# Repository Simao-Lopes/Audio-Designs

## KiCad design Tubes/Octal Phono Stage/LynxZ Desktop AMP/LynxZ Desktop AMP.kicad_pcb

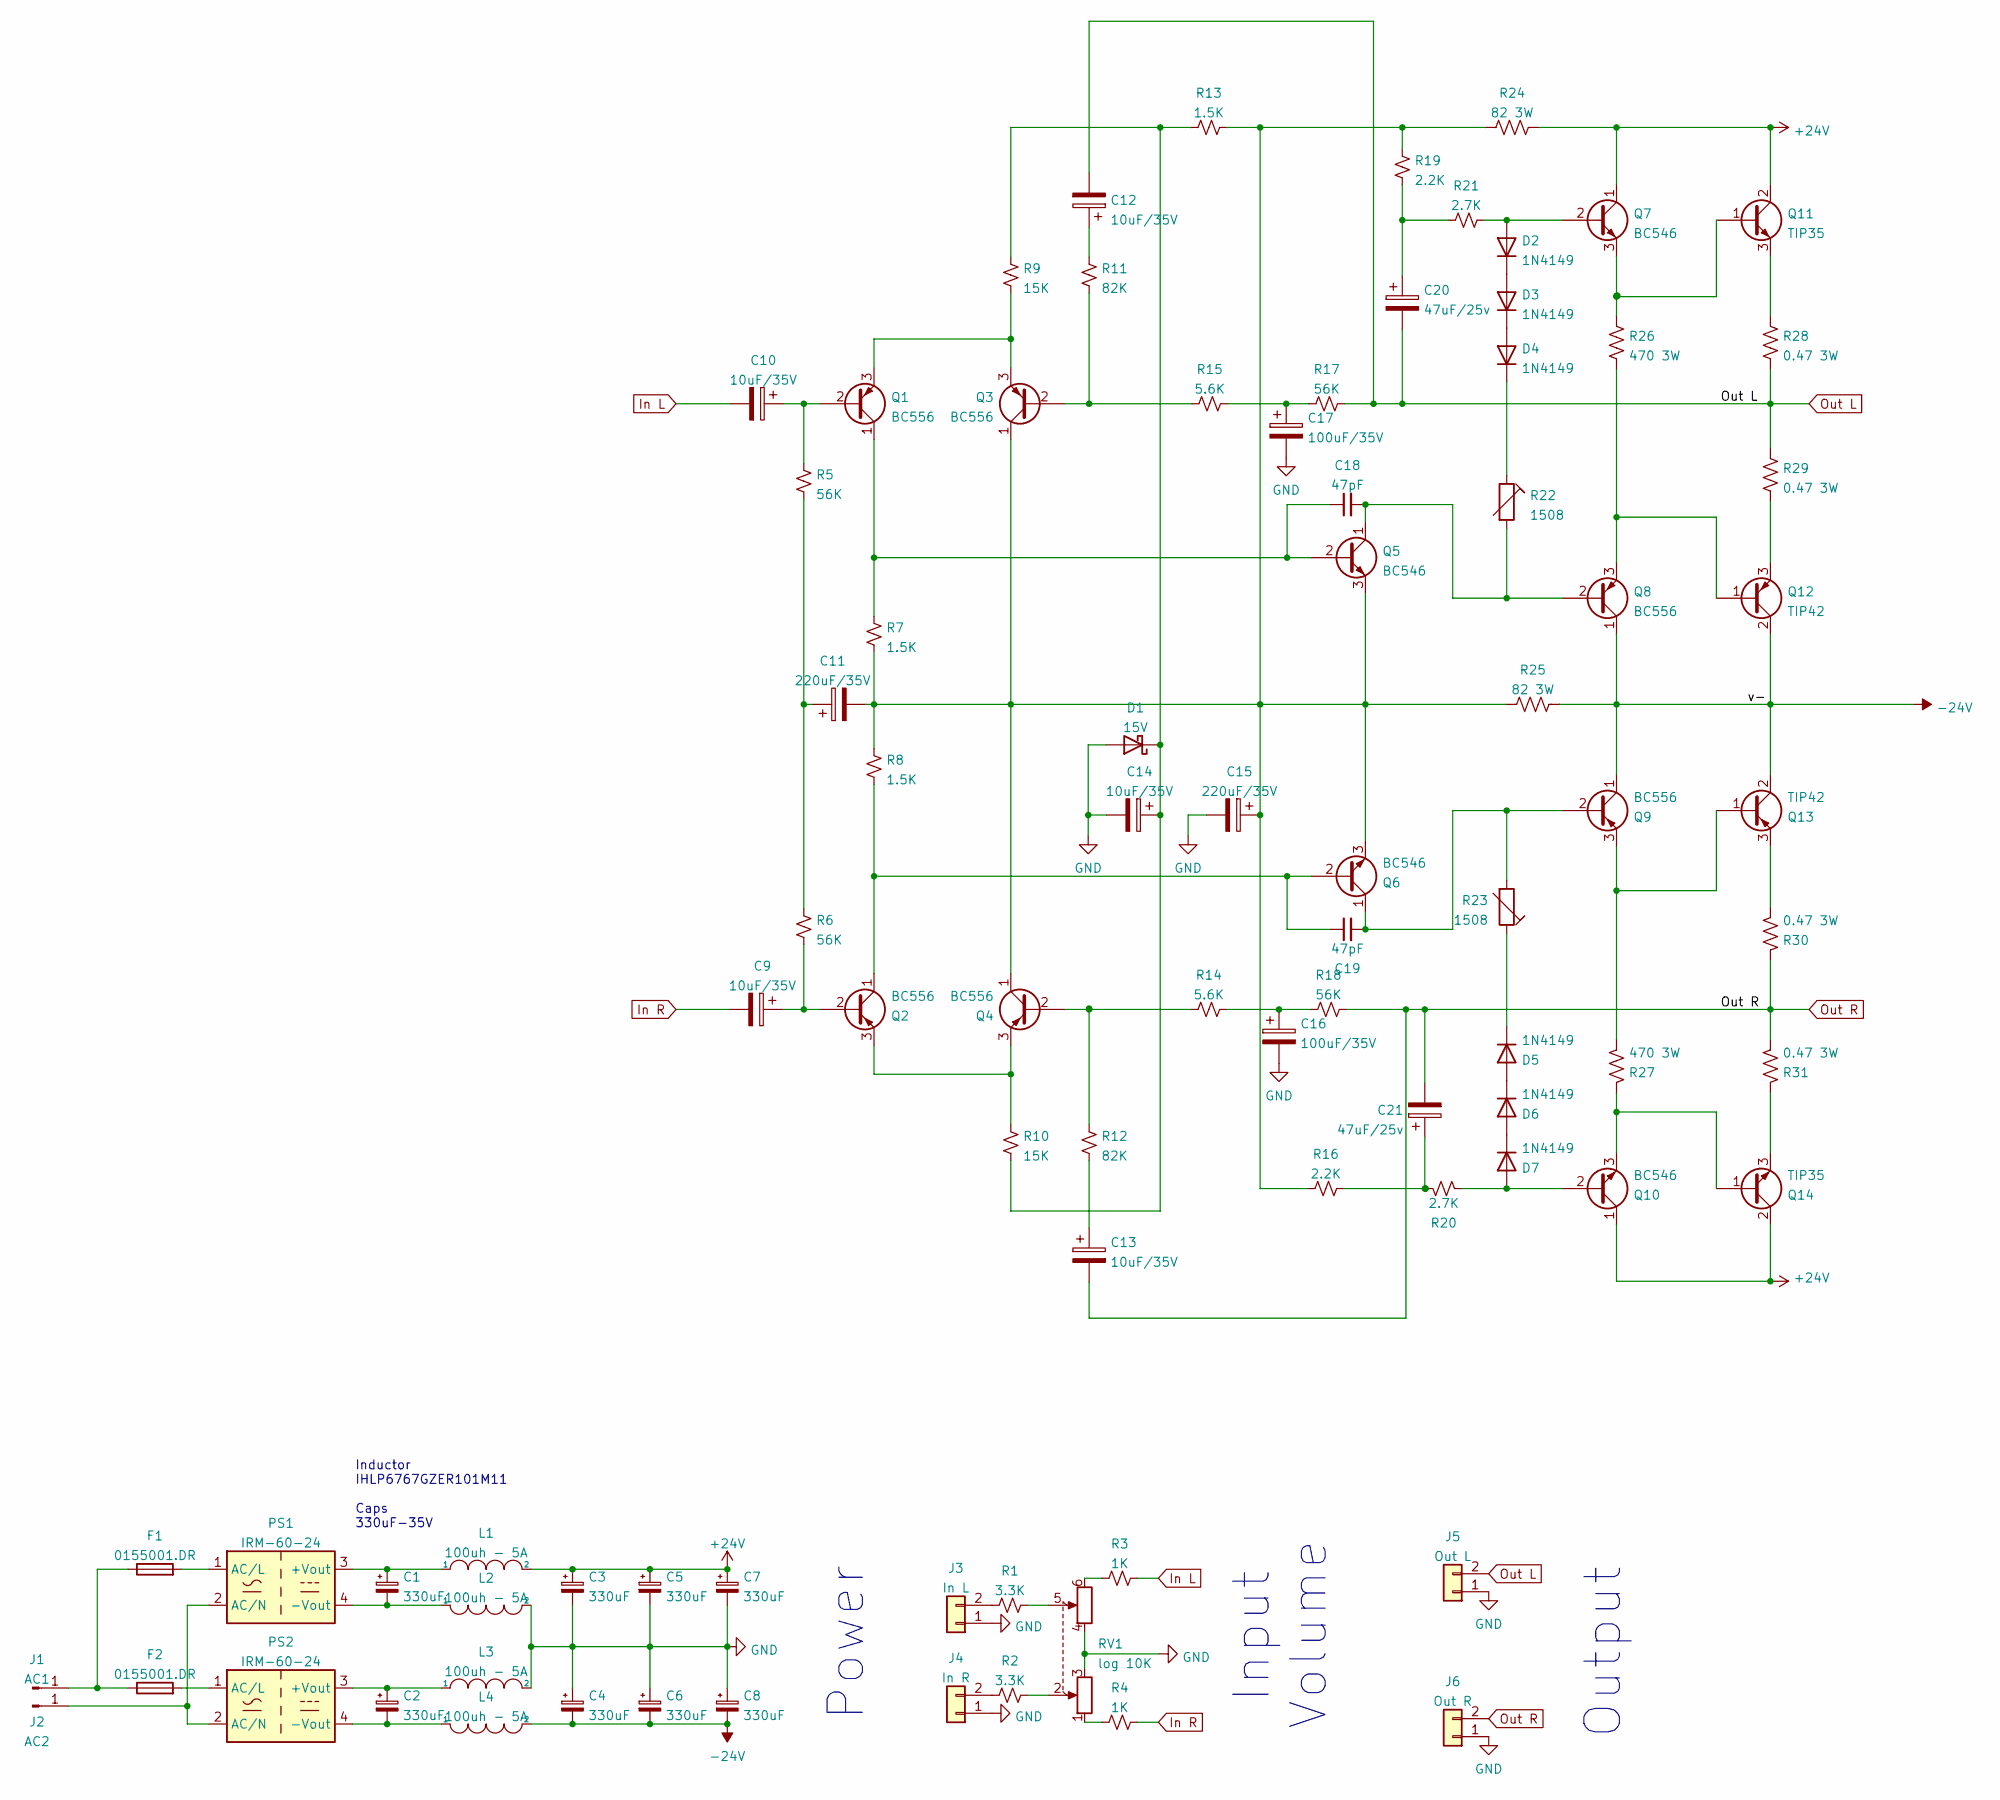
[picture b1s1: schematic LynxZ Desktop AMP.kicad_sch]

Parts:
C1, C2, C3, C4, C5, C6, C7, C8: 330uF; CP_Elec_16x17.5
C9, C10, C12, C13, C14: 10uF/35V; CP_Elec_5x5.3
C11, C15: 220uF/35V; CP_Elec_8x10
C16, C17: 100uF/35V; CP_Elec_8x10
C18, C19: 47pF; C_Rect_L7.2mm_W4.5mm_P5.00mm_FKS2_FKP2_MKS2_MKP2
C20, C21: 47uF/25v; CP_Elec_16x17.5
D1: 15V; D_SMA-SMB_Universal_Handsoldering
D2, D3, D4, D5, D6, D7: 1N4149; D_DO-35_SOD27_P7.62mm_Horizontal
F1, F2: 0155001.DR; Fuseholder_Littelfuse_100_series_5x20mm
J1: AC1; Spade Conector 6.3mm TE_1217861
J2: AC2; Spade Conector 6.3mm TE_1217861
J3: In L; SolderWire-0.5sqmm_1x02_P4.6mm_D0.9mm_OD2.1mm
J4: In R; SolderWire-0.5sqmm_1x02_P4.6mm_D0.9mm_OD2.1mm
J5: Out L; SolderWire-0.5sqmm_1x02_P4.6mm_D0.9mm_OD2.1mm
J6: Out R; SolderWire-0.5sqmm_1x02_P4.6mm_D0.9mm_OD2.1mm
L1, L2, L3, L4: 100uh - 5A; L_Vishay_IHLP-6767
PS1, PS2: IRM-60-24; Converter_ACDC_MeanWell_IRM-60-xx_THT
Q1, Q2, Q3, Q4, Q8, Q9: BC556; TO-92_Inline
Q5, Q6, Q7, Q10: BC546; TO-92_Inline
Q11, Q14: TIP35; TO-247-3_Vertical
Q12, Q13: TIP42; TO-247-3_Vertical
R1, R2: 3.3K; R_1206_3216Metric
R3, R4: 1K; R_1206_3216Metric
R5, R6, R17, R18: 56K; R_1206_3216Metric
R7, R8, R13: 1.5K; R_1206_3216Metric
R9, R10: 15K; R_1206_3216Metric
R11, R12: 82K; R_1206_3216Metric
R14, R15: 5.6K; R_1206_3216Metric
R16, R19: 2.2K; R_1206_3216Metric
R20, R21: 2.7K; R_1206_3216Metric
R22, R23: 1508; R_1206_3216Metric
R24, R25: 82 3W; R_Axial_DIN0617_L17.0mm_D6.0mm_P20.32mm_Horizontal
R26, R27: 470 3W; R_Axial_DIN0617_L17.0mm_D6.0mm_P20.32mm_Horizontal
R28, R29, R30, R31: 0.47 3W; R_Axial_DIN0617_L17.0mm_D6.0mm_P20.32mm_Horizontal
RV1: log 10K; Potentiometer_Alps_RK163_Dual_Horizontal

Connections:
+24V: C3.1, C5.1, C7.1, L1.2, Q7.1 (C), Q10.1 (C), Q11.2 (C), Q14.2 (C), R24.1
-24V: C4.2, C6.2, C8.2, L4.2, Q8.1 (C), Q9.1 (C), Q12.2 (C), Q13.2 (C), R25.1
GND: C3.2, C4.1, C5.2, C6.1, C7.2, C8.1, C14.2, C15.2, C16.2, C17.2, D1.2 (A), J3.1, J4.1, J5.1, J6.1, L2.2, L3.2, RV1.3, RV1.4; also elsewhere on the board
In L: C10.2, R3.2
In R: C9.2, R4.2
unnamed 5: C1.1, L1.1, PS1.3 (+Vout); also elsewhere on the board
unnamed 6: C1.2, L2.1, PS1.4 (-Vout); also elsewhere on the board
unnamed 7: C2.1, L3.1, PS2.3 (+Vout); also elsewhere on the board
unnamed 8: C2.2, L4.1, PS2.4 (-Vout); also elsewhere on the board
unnamed: C9.1, Q2.2 (B), R6.2
unnamed: C10.1, Q1.2 (B), R5.1
unnamed: C11.1, R5.2, R6.1
unnamed: C11.2, C15.1, Q3.1 (C), Q4.1 (C), Q5.3 (E), Q6.3 (E), R7.2, R8.1, R13.2, R16.1, R19.2, R24.2, R25.2
unnamed: C12.1, R11.1
unnamed: C13.1, R12.2
unnamed: C14.1, D1.1 (K), R9.1, R10.2, R13.1
unnamed: C16.1, R14.2, R18.1
unnamed: C17.1, R15.2, R17.1
unnamed: C18.1, Q1.1 (C), Q5.2 (B), R7.1
unnamed 19: C18.2, Q5.1 (C), Q8.2 (B), R22.2; also elsewhere on the board
unnamed: C19.1, Q2.1 (C), Q6.2 (B), R8.2
unnamed 21: C19.2, Q6.1 (C), Q9.2 (B), R23.2; also elsewhere on the board
unnamed: C20.1, R19.1, R21.2
unnamed: C21.1, R16.2, R20.2
unnamed: D2.1 (K), D3.2 (A)
unnamed: D2.2 (A), Q7.2 (B), R21.1
unnamed: D3.1 (K), D4.2 (A)
unnamed 27: D4.1 (K), R22.1; also elsewhere on the board
unnamed 28: D5.1 (K), R23.1; also elsewhere on the board
unnamed: D5.2 (A), D6.1 (K)
unnamed: D6.2 (A), D7.1 (K)
unnamed: D7.2 (A), Q10.2 (B), R20.1
unnamed: F1.1, F2.1, J1.1
unnamed 33: F1.2, PS1.1 (AC/L); also elsewhere on the board
unnamed 34: F2.2, PS2.1 (AC/L); also elsewhere on the board
unnamed 35: J2.1, PS1.2 (AC/N), PS2.2 (AC/N); also elsewhere on the board
unnamed 36: J3.2, R1.1; also elsewhere on the board
unnamed 37: J4.2, R2.1; also elsewhere on the board
unnamed: Q1.3 (E), Q3.3 (E), R9.2
unnamed: Q2.3 (E), Q4.3 (E), R10.1
unnamed: Q3.2 (B), R11.2, R15.1
unnamed: Q4.2 (B), R12.1, R14.1
unnamed 42: Q10.3 (E), Q14.1 (B), R27.1; also elsewhere on the board
unnamed 43: Q7.3 (E), Q11.1 (B), R26.1; also elsewhere on the board
unnamed: Q11.3 (E), R28.1
unnamed 45: Q8.3 (E), Q12.1 (B), R26.2; also elsewhere on the board
unnamed: Q12.3 (E), R29.2
unnamed 47: Q9.3 (E), Q13.1 (B), R27.2; also elsewhere on the board
unnamed: Q13.3 (E), R30.2
unnamed: Q14.3 (E), R31.1
unnamed: R1.2, RV1.5
unnamed: R2.2, RV1.2
unnamed: R3.1, RV1.6
unnamed: R4.1, RV1.1
Out L: C12.2, C20.2, J5.2, R17.2, R28.2, R29.1; also elsewhere on the board
Out R: C13.2, C21.2, J6.2, R18.2, R30.1, R31.2; also elsewhere on the board

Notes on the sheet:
Power
Input Volume
Inductor IHLP6767GZER101M11 Caps 330uF-35V
Output

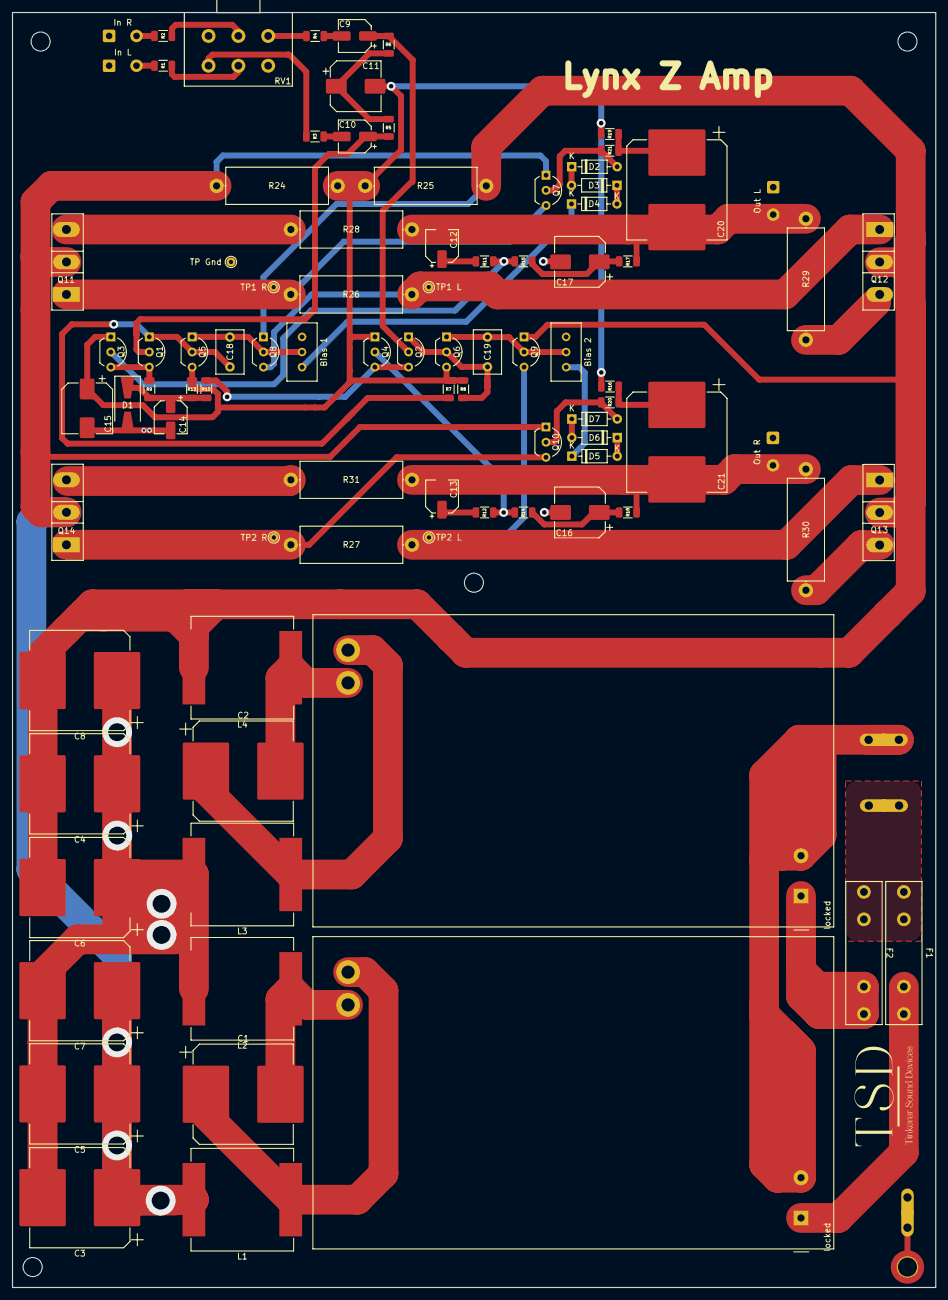
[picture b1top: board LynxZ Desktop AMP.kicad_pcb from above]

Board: 2 copper layers, 154.9 x 213.9 mm, 94 parts (0 on the bottom side), 56 nets.

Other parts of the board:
Bias 1, Bias 2: 1508; Potentiometer_Bourns_3296W_Vertical
In L: In L; SolderWire-0.5sqmm_1x02_P4.6mm_D0.9mm_OD2.1mm
In R: In R; SolderWire-0.5sqmm_1x02_P4.6mm_D0.9mm_OD2.1mm
J2#2: AC2; Spade Conector 6.3mm TE_1217861
Out L: Out L; SolderWire-0.5sqmm_1x02_P4.6mm_D0.9mm_OD2.1mm
Out R: Out R; SolderWire-0.5sqmm_1x02_P4.6mm_D0.9mm_OD2.1mm
TP1 L, TP1 R, TP2 L, TP2 R: TestPoint_THTPad_D1.5mm_Drill0.7mm
TP Gnd: TestPoint_THTPad_D1.5mm_Drill0.7mm
locked: IRM-60-24; Converter_ACDC_MeanWell_IRM-60-xx_THT
locked#2: IRM-60-24; Converter_ACDC_MeanWell_IRM-60-xx_THT

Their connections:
GND: In L.1, In R.1, Out L.1, Out R.1, TP Gnd.1; also elsewhere on the board
unnamed 5: locked.3 (+Vout); also elsewhere on the board
unnamed 6: locked.4 (-Vout); also elsewhere on the board
unnamed 7: locked#2.3 (+Vout); also elsewhere on the board
unnamed 8: locked#2.4 (-Vout); also elsewhere on the board
unnamed 19: Bias 1.2; also elsewhere on the board
unnamed 21: Bias 2.2; also elsewhere on the board
unnamed 27: Bias 1.1; also elsewhere on the board
unnamed 28: Bias 2.1; also elsewhere on the board
unnamed 33: locked.1 (AC/L); also elsewhere on the board
unnamed 34: locked#2.1 (AC/L); also elsewhere on the board
unnamed 35: locked.2 (AC/N), locked#2.2 (AC/N); also elsewhere on the board
unnamed 36: In L.2; also elsewhere on the board
unnamed 37: In R.2; also elsewhere on the board
unnamed 42: TP2 R.1; also elsewhere on the board
unnamed 43: TP1 R.1; also elsewhere on the board
unnamed 45: TP1 L.1; also elsewhere on the board
unnamed 47: TP2 L.1; also elsewhere on the board
Out L: Out L.2; also elsewhere on the board
Out R: Out R.2; also elsewhere on the board

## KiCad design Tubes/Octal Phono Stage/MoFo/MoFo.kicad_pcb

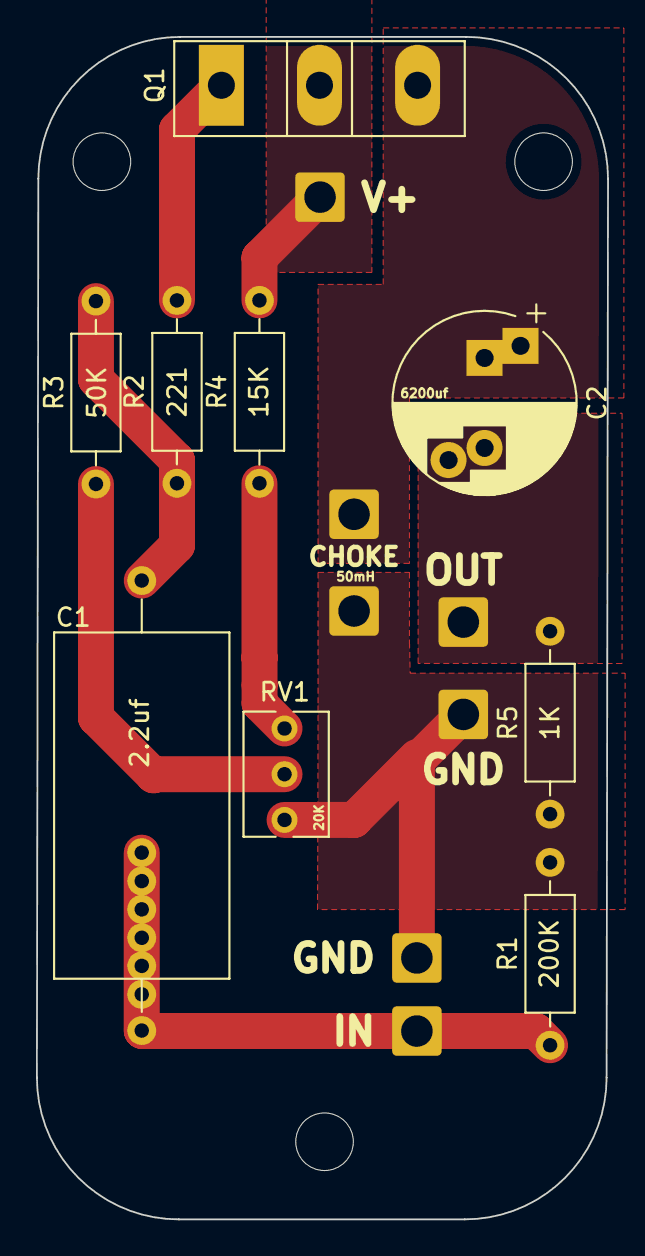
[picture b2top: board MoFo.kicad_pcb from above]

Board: 2 copper layers, 31.7 x 65.7 mm, 16 parts (0 on the bottom side), 9 nets.

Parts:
50mH: L1; SolderWire-1sqmm_1x01_D1.4mm_OD2.7mm
C1: 2.2uf; C_Axial_L19.0mm_D9.5mm_P25.00mm_Horizontal
C2: 6200uf; CP_Radial_D10.0mm_P5.00mm_P7.50mm
CHOKE: IN; SolderWire-1sqmm_1x01_D1.4mm_OD2.7mm
IN: IN; SolderWire-1sqmm_1x01_D1.4mm_OD2.7mm
IN#2: INGND; SolderWire-1sqmm_1x01_D1.4mm_OD2.7mm
J3: OUTGND; SolderWire-1sqmm_1x01_D1.4mm_OD2.7mm
OUT: OUT; SolderWire-1sqmm_1x01_D1.4mm_OD2.7mm
Q1: IRF250/240; TO-247-3_Vertical
R1: 200K; R_Axial_DIN0207_L6.3mm_D2.5mm_P10.16mm_Horizontal
R2: 221; R_Axial_DIN0207_L6.3mm_D2.5mm_P10.16mm_Horizontal
R3: 50K; R_Axial_DIN0207_L6.3mm_D2.5mm_P10.16mm_Horizontal
R4: 15K; R_Axial_DIN0207_L6.3mm_D2.5mm_P10.16mm_Horizontal
R5: 1K; R_Axial_DIN0207_L6.3mm_D2.5mm_P10.16mm_Horizontal
RV1: 20K; Potentiometer_Bourns_3266Y_Vertical
V+: V; SolderWire-1sqmm_1x01_D1.4mm_OD2.7mm

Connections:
/ADJ: R3.2, RV1.2
/INDUCTOR: 50mH.1, C2.1, Q1.3 (S)
/OUT: C2.2, OUT.1, R5.1
/SGN: C1.2, R2.1, R3.1
/V_IN: Q1.2 (D), R4.2, V+.1
GND: CHOKE.1, IN#2.1, J3.1, R1.2, R5.2, RV1.3
unnamed: C1.1, IN.1, R1.1
unnamed: Q1.1 (G), R2.2
unnamed: R4.1, RV1.1

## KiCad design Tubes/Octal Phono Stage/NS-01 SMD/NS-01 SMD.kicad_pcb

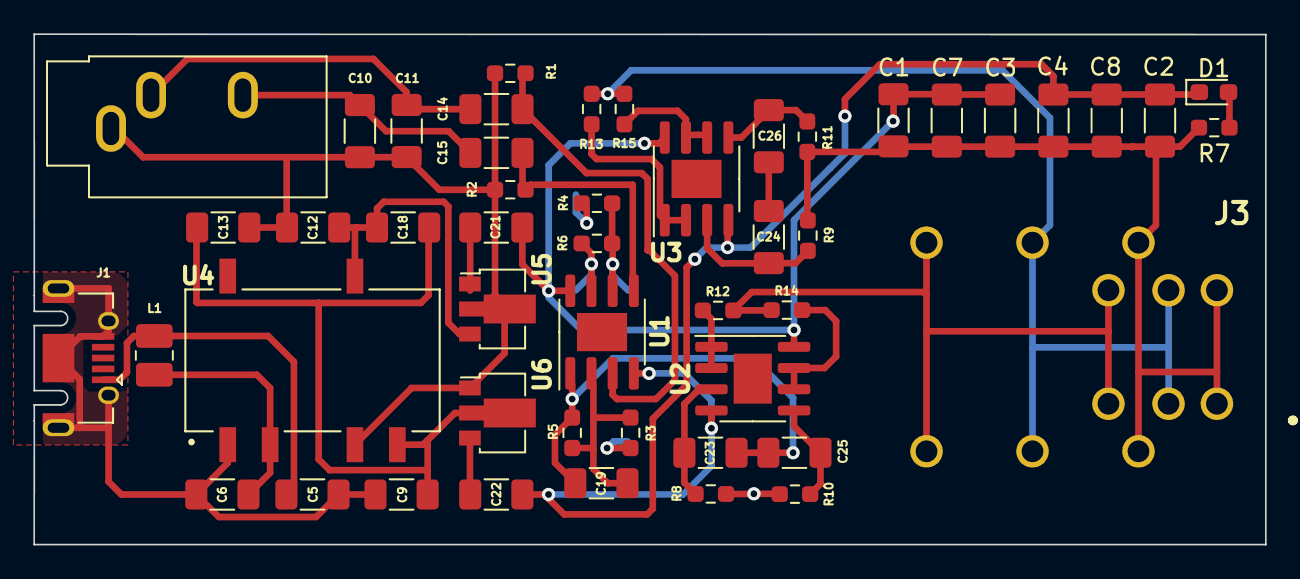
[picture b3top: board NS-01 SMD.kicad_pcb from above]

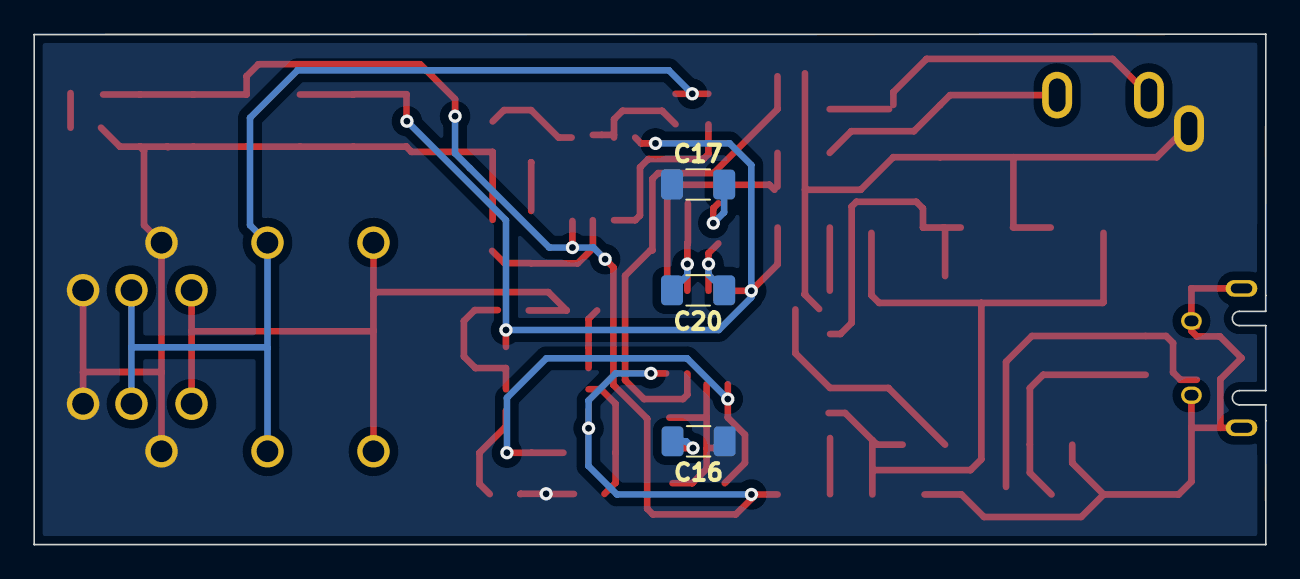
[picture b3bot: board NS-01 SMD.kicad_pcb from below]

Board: 2 copper layers, 73.8 x 30.6 mm, 52 parts (3 on the bottom side), 32 nets.

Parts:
C1, C2, C3, C4, C7, C8: 100nf; C_1206_3216Metric_Pad1.33x1.80mm_HandSolder
C5, C6: 4u7; C_1206_3216Metric_Pad1.33x1.80mm_HandSolder
C9: 1nf/4kv; C_1206_3216Metric_Pad1.33x1.80mm_HandSolder
C10, C11, C19, C20: 68pf; C_1206_3216Metric_Pad1.33x1.80mm_HandSolder
C12, C13, C14, C15, C16, C17, C18, C23, C24, C25, C26: 1uf; C_1206_3216Metric_Pad1.33x1.80mm_HandSolder
C21, C22: 2u2; C_1206_3216Metric_Pad1.33x1.80mm_HandSolder
D1: LED; D_0603_1608Metric_Pad1.05x0.95mm_HandSolder
J1: USB_B_Mini; USB_Micro-AB_Molex_47590-0001
J2: AudioJack3; Jack_3.5mm_CUI_SJ1-3533NG_Horizontal
J3: AudioJack3; ACJSMHD985
L1: 6.8uh; L_1008_2520Metric_Pad1.43x2.20mm_HandSolder
R1, R2, R3, R4, R5, R6, R7, R8, R9, R10, R11: 10k; R_0603_1608Metric_Pad0.98x0.95mm_HandSolder
R12, R13, R14, R15: 1R; R_0603_1608Metric_Pad0.98x0.95mm_HandSolder
U1, U2, U3: OPA1678; SOIC-8-1EP_3.9x4.9mm_P1.27mm_EP2.29x3mm
U4: PESE1-S5-D12-M; CONV_PESE1-S5-D12-M
U5: L78L10_SOT89; SOT-89-3
U6: L79L12_SOT89; SOT-89-3

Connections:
/R_OUT: J3.R, R13.2, R15.2
/T_IN: C11.2, C14.2, J2.T
/T_OUT: J3.T, R12.2, R14.2
GND: C1.1, C2.2, C3.1, C4.2, C7.1, C8.2, C10.1, C11.1, C12.2, C13.1, C16.1, C17.1, J2.S, J3.S, R1.1, R2.1, R7.1, R8.1, R9.1, R10.1, R11.1, U4.4 (0V), U5.2 (GND), U6.1 (GND)
unnamed: C5.1, J1.1 (VBUS), L1.1
unnamed: C5.2, C6.1, C9.1, J1.5 (GND), J1.6 (Shield), U4.1 (VIN-)
unnamed: C6.2, L1.2, U4.2 (VIN+)
unnamed: C10.2, C15.2, J2.R
unnamed: C12.1, C18.1, U4.7 (VOUT+), U5.3 (IN)
unnamed: C9.2, C13.2, C18.2, U4.5 (VOUT-), U6.2 (VI)
unnamed: C14.1, R1.2, U1.3 (+)
unnamed: C15.1, R2.2, U1.5 (+)
unnamed: C16.2, R3.2
unnamed: C17.2, R4.2
unnamed: C19.1, C23.2, C25.2, R5.2, U1.1
unnamed: C19.2, R3.1, R5.1, U1.2 (-)
unnamed: C20.1, R6.2, U1.7
unnamed: C20.2, R4.1, R6.1, U1.6 (-)
unnamed: C21.1, U5.1 (OUT)
unnamed: C22.1, U6.3 (VO)
unnamed: C23.1, R8.2, U2.3 (+)
unnamed: C24.1, R9.2, U3.3 (+)
unnamed: C24.2, C26.2
unnamed: C25.1, R10.2, U2.5 (+)
unnamed: C26.1, R11.2, U3.5 (+)
unnamed: D1.2 (A), R7.2
unnamed: R12.1, U2.1, U2.2 (-)
unnamed: R13.1, U3.1, U3.2 (-)
unnamed: R14.1, U2.6 (-), U2.7
unnamed: R15.1, U3.6 (-), U3.7
VCC: C1.2, C3.2, C7.2, C21.2, U1.8 (V+), U2.8 (V+), U3.8 (V+)
VEE: C2.1, C4.1, C8.1, C22.2, D1.1 (K), U1.4 (V-), U2.4 (V-), U3.4 (V-)

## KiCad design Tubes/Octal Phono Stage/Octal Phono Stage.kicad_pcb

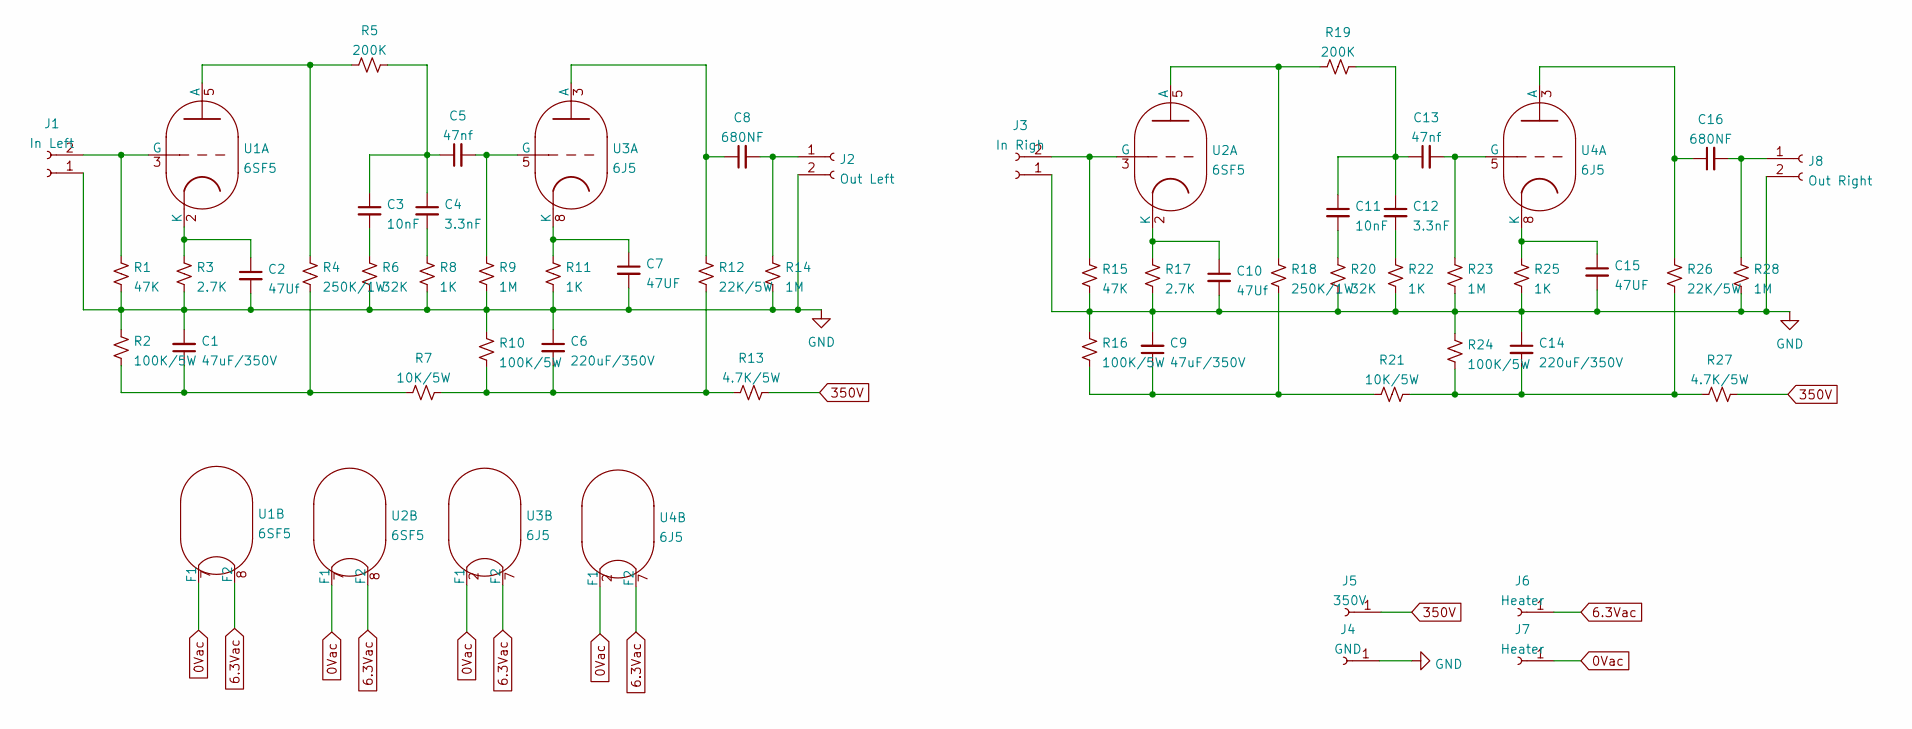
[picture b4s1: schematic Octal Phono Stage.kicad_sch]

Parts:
C1, C9: 47uF/350V; C_Rect_L31.5mm_W13.0mm_P27.50mm_MKS4
C2, C10: 47Uf; C_Rect_L31.5mm_W13.0mm_P27.50mm_MKS4
C3, C11: 10nF; C_Rect_L31.5mm_W13.0mm_P27.50mm_MKS4
C4, C12: 3.3nF; C_Rect_L31.5mm_W13.0mm_P27.50mm_MKS4
C5, C13: 47nf; C_Rect_L31.5mm_W13.0mm_P27.50mm_MKS4
C6, C14: 220uF/350V; C_Rect_L31.5mm_W13.0mm_P27.50mm_MKS4
C7, C15: 47UF; C_Rect_L31.5mm_W13.0mm_P27.50mm_MKS4
C8, C16: 680NF; C_Rect_L31.5mm_W13.0mm_P27.50mm_MKS4
J1: In Left; SolderWire-0.75sqmm_1x02_P4.8mm_D1.25mm_OD2.3mm
J2: Out Left; SolderWire-0.75sqmm_1x02_P4.8mm_D1.25mm_OD2.3mm
J3: In Righ; SolderWire-0.75sqmm_1x02_P4.8mm_D1.25mm_OD2.3mm
J4: GND; SolderWire-0.75sqmm_1x01_D1.25mm_OD2.3mm
J5: 350V; SolderWire-0.75sqmm_1x01_D1.25mm_OD2.3mm
J6, J7: Heater; SolderWire-0.75sqmm_1x01_D1.25mm_OD2.3mm
J8: Out Right; SolderWire-0.75sqmm_1x02_P4.8mm_D1.25mm_OD2.3mm
R1, R15: 47K; R_Axial_DIN0207_L6.3mm_D2.5mm_P15.24mm_Horizontal
R2, R10, R16, R24: 100K/5W; R_Axial_DIN0922_L20.0mm_D9.0mm_P25.40mm_Horizontal
R3, R17: 2.7K; R_Axial_DIN0207_L6.3mm_D2.5mm_P15.24mm_Horizontal
R4: 250K/1W; R_Axial_DIN0411_L9.9mm_D3.6mm_P15.24mm_Horizontal
R5, R19: 200K; R_Axial_DIN0207_L6.3mm_D2.5mm_P15.24mm_Horizontal
R6, R20: 32K; R_Axial_DIN0207_L6.3mm_D2.5mm_P15.24mm_Horizontal
R7, R21: 10K/5W; R_Axial_DIN0922_L20.0mm_D9.0mm_P25.40mm_Horizontal
R8, R11, R22, R25: 1K; R_Axial_DIN0207_L6.3mm_D2.5mm_P15.24mm_Horizontal
R9, R14, R23, R28: 1M; R_Axial_DIN0207_L6.3mm_D2.5mm_P15.24mm_Horizontal
R12, R26: 22K/5W; R_Axial_DIN0922_L20.0mm_D9.0mm_P25.40mm_Horizontal
R13, R27: 4.7K/5W; R_Axial_DIN0922_L20.0mm_D9.0mm_P25.40mm_Horizontal
R18: 250K/1W; R_Axial_DIN0922_L20.0mm_D9.0mm_P25.40mm_Horizontal
U1, U2: 6SF5; Valve_Octal
U3, U4: 6J5; Valve_Octal

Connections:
0Vac: J7.1, U1.7 (F1), U2.7 (F1), U3.2 (F1), U4.2 (F1)
6.3Vac: J6.1, U1.8 (F2), U2.8 (F2), U3.7 (F2), U4.7 (F2)
350V: J5.1, R13.2, R27.2
GND: C1.2, C2.2, C6.1, C7.2, C9.2, C10.2, C14.1, C15.2, J1.1, J2.2, J3.1, J4.1, J8.2, R1.2, R2.1, R3.2, R6.2, R8.2, R9.2, R10.1, R11.2, R14.2, R15.2, R16.1, R17.2, R20.2, R22.2, R23.2, R24.1, R25.2, R28.2
unnamed: C1.1, R2.2, R4.2, R7.1
unnamed: C2.1, R3.1, U1.2 (K)
unnamed: C3.1, C4.1, C5.1
unnamed: C3.2, R6.1
unnamed: C4.2, R8.1
unnamed: C5.2, R9.1, U3.5 (G)
unnamed: C6.2, R7.2, R10.2, R12.2, R13.1
unnamed: C7.1, R11.1, U3.8 (K)
unnamed: C8.1, R12.1, U3.3 (A)
unnamed: C8.2, J2.1, R14.1
unnamed: C9.1, R16.2, R18.2, R21.1
unnamed: C10.1, R17.1, U2.2 (K)
unnamed: C11.1, C12.1, C13.1
unnamed: C11.2, R20.1
unnamed: C12.2, R22.1
unnamed: C13.2, R23.1, U4.5 (G)
unnamed: C14.2, R21.2, R24.2, R26.2, R27.1
unnamed: C15.1, R25.1, U4.8 (K)
unnamed: C16.1, R26.1, U4.3 (A)
unnamed: C16.2, J8.1, R28.1
unnamed: J1.2, R1.1, U1.3 (G)
unnamed: J3.2, R15.1, U2.3 (G)
unnamed: R4.1, R5.1, U1.5 (A)
unnamed: R18.1, R19.1, U2.5 (A)

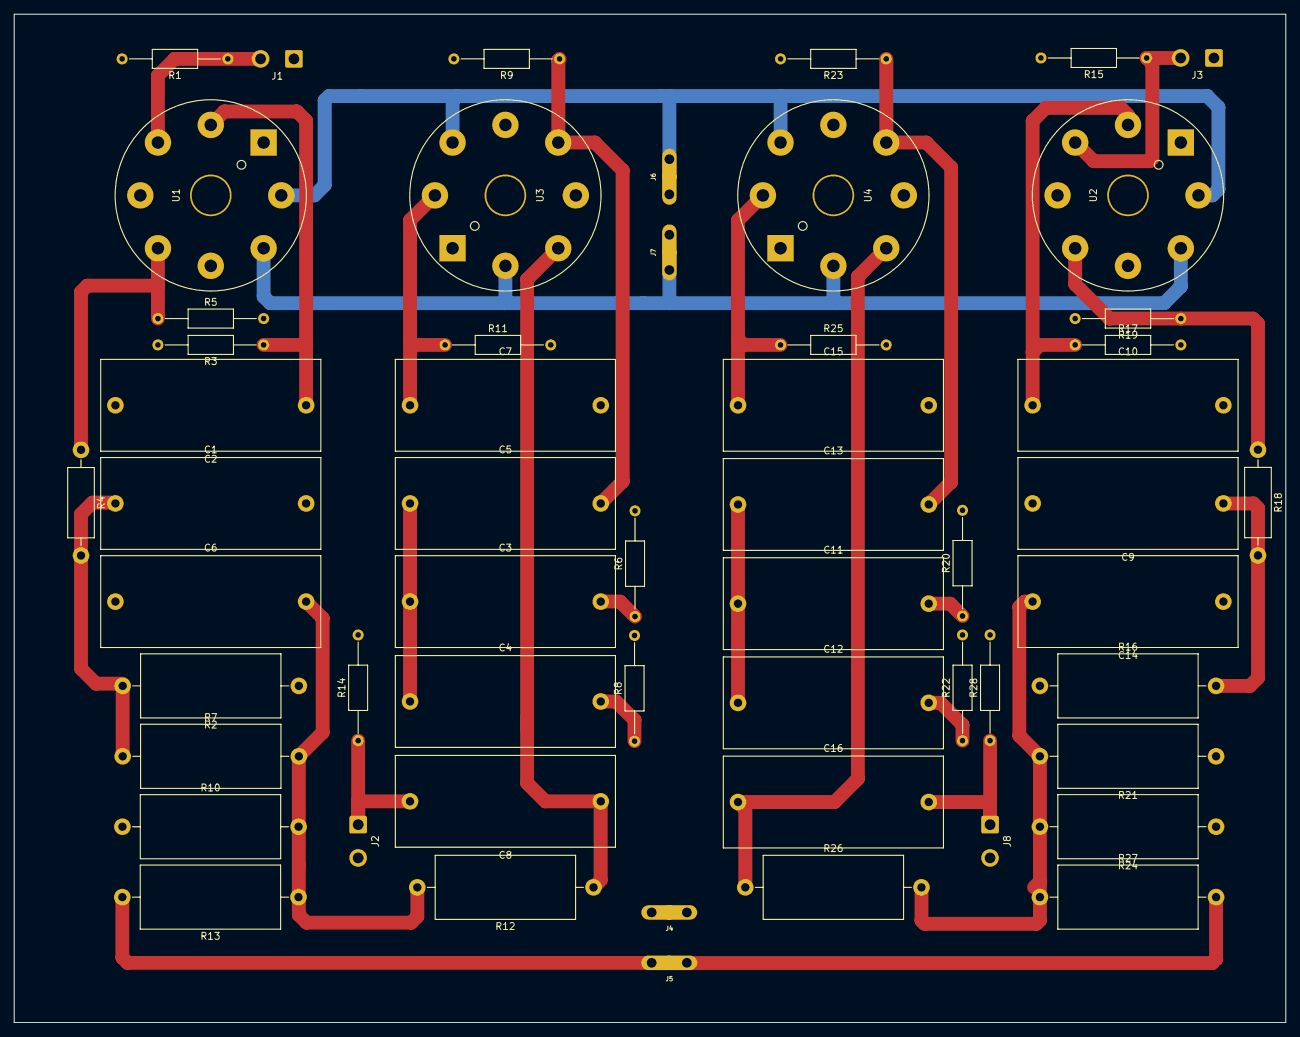
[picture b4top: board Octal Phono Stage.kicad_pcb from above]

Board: 2 copper layers, 183.3 x 145.4 mm, 56 parts (0 on the bottom side), 28 nets.

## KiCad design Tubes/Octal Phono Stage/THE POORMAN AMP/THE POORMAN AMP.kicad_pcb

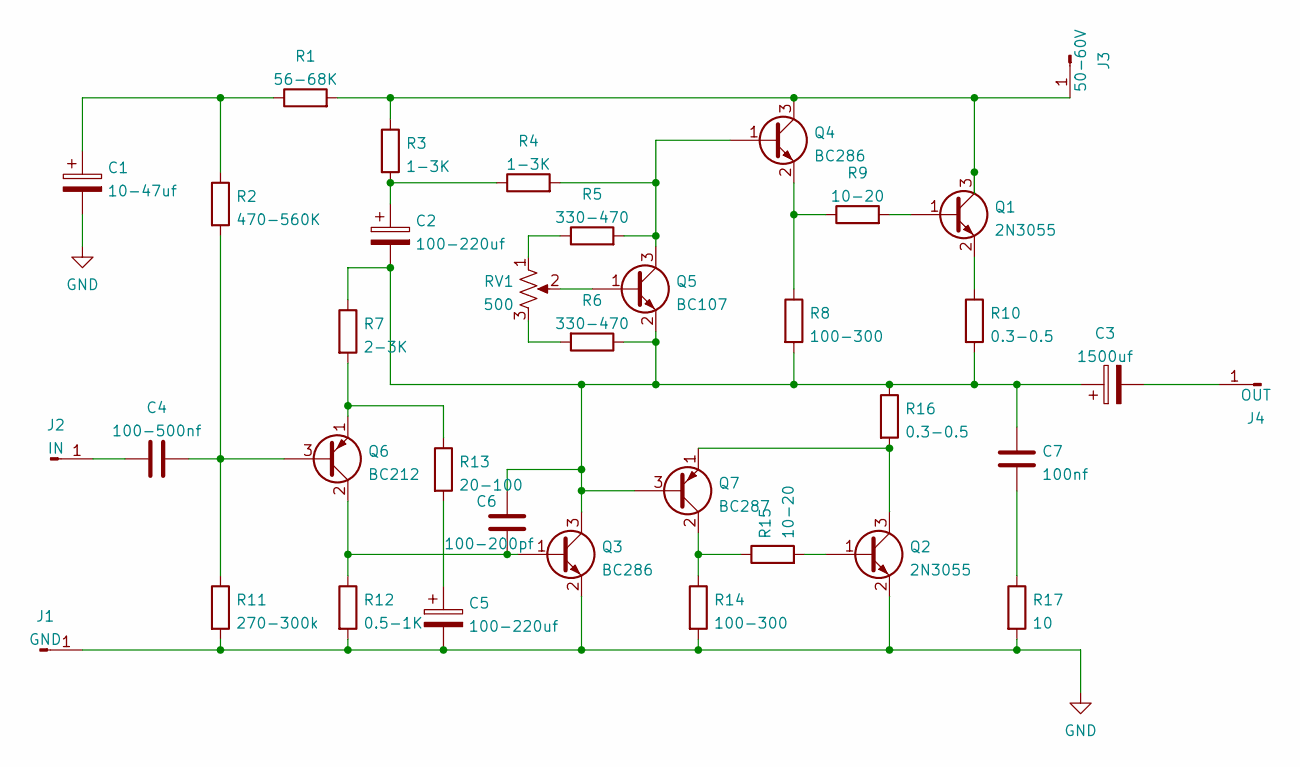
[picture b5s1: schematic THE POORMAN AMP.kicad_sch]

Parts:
C1: 10-47uf; CP_Radial_D10.0mm_P5.00mm_P7.50mm
C2, C5: 100-220uf; CP_Radial_D10.0mm_P5.00mm_P7.50mm
C3: 1500uf; CP_Radial_D18.0mm_P7.50mm
C4: 100-500nf; C_Rect_L7.2mm_W4.5mm_P5.00mm_FKS2_FKP2_MKS2_MKP2
C6: 100-200pf; C_Rect_L7.2mm_W4.5mm_P5.00mm_FKS2_FKP2_MKS2_MKP2
C7: 100nf; C_Rect_L7.2mm_W4.5mm_P5.00mm_FKS2_FKP2_MKS2_MKP2
J1: GND; M4_Screw_Terminal
J2: IN; SolderWire-1.5sqmm_1x01_D1.7mm_OD3.9mm
J3: 50-60V; M4_Screw_Terminal
J4: OUT; M4_Screw_Terminal
Q1, Q2: 2N3055; TO-3
Q3, Q4: BC286; TO-39-3
Q5: BC107; TO-18-3
Q6: BC212; TO-92L_Inline_Wide
Q7: BC287; TO-39-3
R1: 56-68K; R_Axial_DIN0207_L6.3mm_D2.5mm_P7.62mm_Horizontal
R2: 470-560K; R_Axial_DIN0207_L6.3mm_D2.5mm_P7.62mm_Horizontal
R3, R4: 1-3K; R_Axial_DIN0207_L6.3mm_D2.5mm_P7.62mm_Horizontal
R5, R6: 330-470; R_Axial_DIN0207_L6.3mm_D2.5mm_P7.62mm_Horizontal
R7: 2-3K; R_Axial_DIN0207_L6.3mm_D2.5mm_P7.62mm_Horizontal
R8, R14: 100-300; R_Axial_DIN0207_L6.3mm_D2.5mm_P7.62mm_Horizontal
R9, R15: 10-20; R_Axial_DIN0207_L6.3mm_D2.5mm_P7.62mm_Horizontal
R10, R16: 0.3-0.5; R_Axial_Power_L25.0mm_W9.0mm_P27.94mm
R11: 270-300k; R_Axial_DIN0207_L6.3mm_D2.5mm_P7.62mm_Horizontal
R12: 0.5-1K; R_Axial_DIN0207_L6.3mm_D2.5mm_P7.62mm_Horizontal
R13: 20-100; R_Axial_DIN0207_L6.3mm_D2.5mm_P7.62mm_Horizontal
R17: 10; R_Axial_DIN0207_L6.3mm_D2.5mm_P7.62mm_Horizontal
RV1: 500; Potentiometer_Bourns_3296W_Vertical

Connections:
GND: C1.2, C5.2, J1.1, Q2.2 (E), Q3.2 (E), R11.2, R12.2, R14.2, R17.2
unnamed: C1.1, R1.1, R2.1
unnamed: C2.1, R3.2, R4.1
unnamed: C2.2, C3.1, C6.1, C7.1, Q3.3 (C), Q5.2 (E), Q7.3 (B), R6.1, R7.1, R8.2, R10.2, R16.1
unnamed: C3.2, J4.1
unnamed 5: C4.1, J2.1; also elsewhere on the board
unnamed: C4.2, Q6.3 (B), R2.2, R11.1
unnamed: C5.1, R13.2
unnamed: C6.2, Q3.1 (B), Q6.2 (C), R12.1
unnamed: C7.2, R17.1
unnamed: J3.1, Q1.3 (C), Q4.3 (C), R1.2, R3.1
unnamed: Q1.1 (B), R9.2
unnamed: Q1.2 (E), R10.1
unnamed: Q2.1 (B), R15.2
unnamed: Q2.3 (C), Q7.1 (E), R16.2
unnamed: Q4.1 (B), Q5.3 (C), R4.2, R5.2
unnamed: Q4.2 (E), R8.1, R9.1
unnamed: Q5.1 (B), RV1.2
unnamed: Q6.1 (E), R7.2, R13.1
unnamed: Q7.2 (C), R14.1, R15.1
unnamed: R5.1, RV1.1
unnamed: R6.2, RV1.3

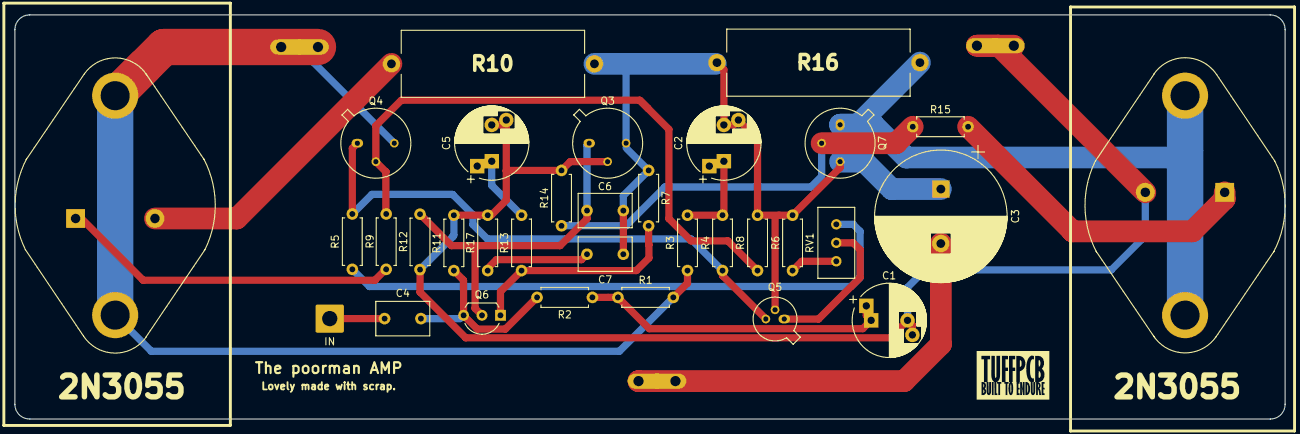
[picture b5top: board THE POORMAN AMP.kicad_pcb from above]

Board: 2 copper layers, 174.8 x 55.6 mm, 36 parts (0 on the bottom side), 22 nets.

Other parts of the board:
IN: IN; SolderWire-1.5sqmm_1x01_D1.7mm_OD3.9mm

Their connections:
unnamed 5: IN.1; also elsewhere on the board

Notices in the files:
parts and their libraries:
Copyright 2016 Accelerated Designs. All rights reserved.
